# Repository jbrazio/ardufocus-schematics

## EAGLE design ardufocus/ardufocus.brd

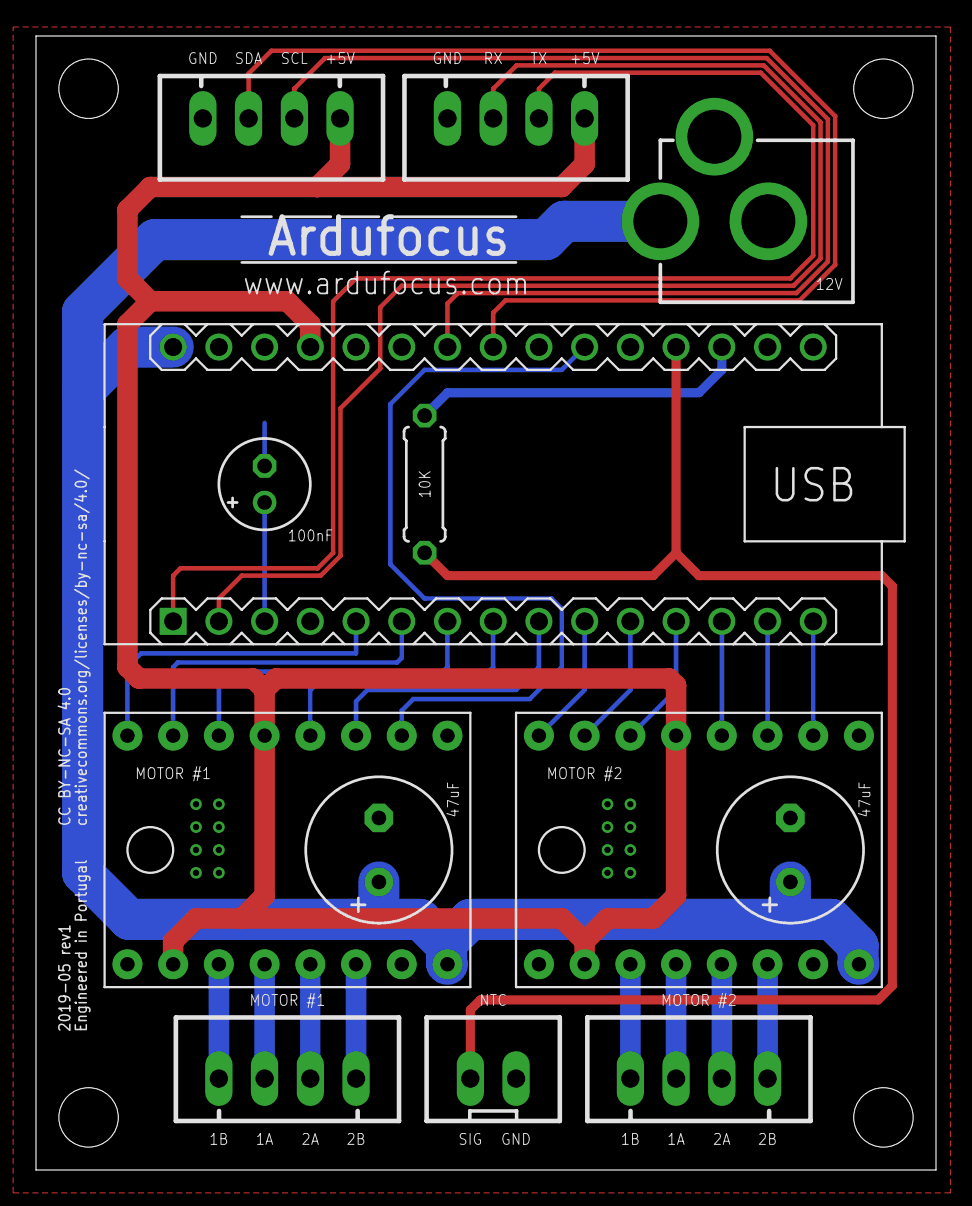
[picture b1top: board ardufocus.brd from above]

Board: 2 copper layers, 50.0 x 63.0 mm, 18 parts (1 on the bottom side), 31 nets.

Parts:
C1: 100nF; E2-5
C2, C3: 47uF; E3,5-8
J5: POWER_JACK; POWER_JACK_PTH
M1: ARDUINO-NANO-3.0
OUT1, OUT2: BOARD_A4988
PGRM: JUMPER-SMT_2_NO_SILK; SMT-JUMPER_2_NO_SILK
R1: 10K; 0207/7
U$1, U$2, U$3, U$4: STAND-OFF
X2, X3, X4, X5: JST-XH-04-PIN-LONG-PAD; JST-XH-04-PACKAGE-LONG-PAD
X6: JST-XH-02-PIN-LONG-PAD; JST-XH-02-PACKAGE-LONG-PAD

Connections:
+5V: M1.J2.4, OUT1.+5V, OUT1.RESET, OUT2.+5V, OUT2.RESET, X4.1, X5.1
+12V: C2.+, C3.+, J5.PWR, M1.J2.1, OUT1.VMOT, OUT2.VMOT
A0: M1.J2.12, R1.2, X6.1
A2: M1.J2.10, OUT1.MS1
AREF: M1.J2.13, R1.1
D2: M1.J1.5, OUT1.DIR
D3: M1.J1.6, OUT1.STEP
D4: M1.J1.7, OUT1.SLEEP
D5: M1.J1.8, OUT1.MS3
D6: M1.J1.9, OUT1.MS2
D7: M1.J1.10, OUT2.DIR
D8: M1.J1.11, OUT2.STEP
D9: M1.J1.12, OUT2.SLEEP
D10: M1.J1.13, OUT2.MS3
D11: M1.J1.14, OUT2.MS2
D12: M1.J1.15, OUT2.MS1
GND: C2.-, C3.-, J5.GND, M1.J1.4, M1.J2.2, OUT1.ENABLE, OUT1.GND, OUT1.GNDMOT, OUT2.ENABLE, OUT2.GND, OUT2.GNDMOT, PGRM.2, X4.4, X5.4, X6.2
unnamed: OUT2.M1B, X3.1
unnamed: C1.-, PGRM.1
unnamed: OUT1.M2A, X2.3
unnamed: OUT2.M1A, X3.2
unnamed: OUT2.M2AB, X3.4
unnamed: OUT1.M1B, X2.1
unnamed: OUT1.M1A, X2.2
unnamed: OUT1.M2AB, X2.4
unnamed: OUT2.M2A, X3.3
RST: C1.+, M1.J1.3
RX: M1.J1.2, X4.3
SCL: M1.J2.7, X5.2
SDA: M1.J2.8, X5.3
TX: M1.J1.1, X4.2

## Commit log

2019-05-17 Project import
2019-05-17 Overall board revision
2019-05-20 Miscellaneous changes
2022-08-04 New PCB layout
2022-08-04 Revert "New PCB layout"
    This reverts commit abb039d9954214917f7d505cd5213ebb6519a360.

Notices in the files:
ardufocus/ardufocus.brd:
CC BY-NC-SA 4.0
creativecommons.org/licenses/by-nc-sa/4.0
parts and their libraries:
diy-modules: Released under the Creative Commons Attribution 4.0 International License: http://creativecommons.org/licenses/by/4.0
SparkFun-Hardware: Licensing: Creative Commons ShareAlike 4.0 International - https://creativecommons.org/licenses/by-sa/4.0
